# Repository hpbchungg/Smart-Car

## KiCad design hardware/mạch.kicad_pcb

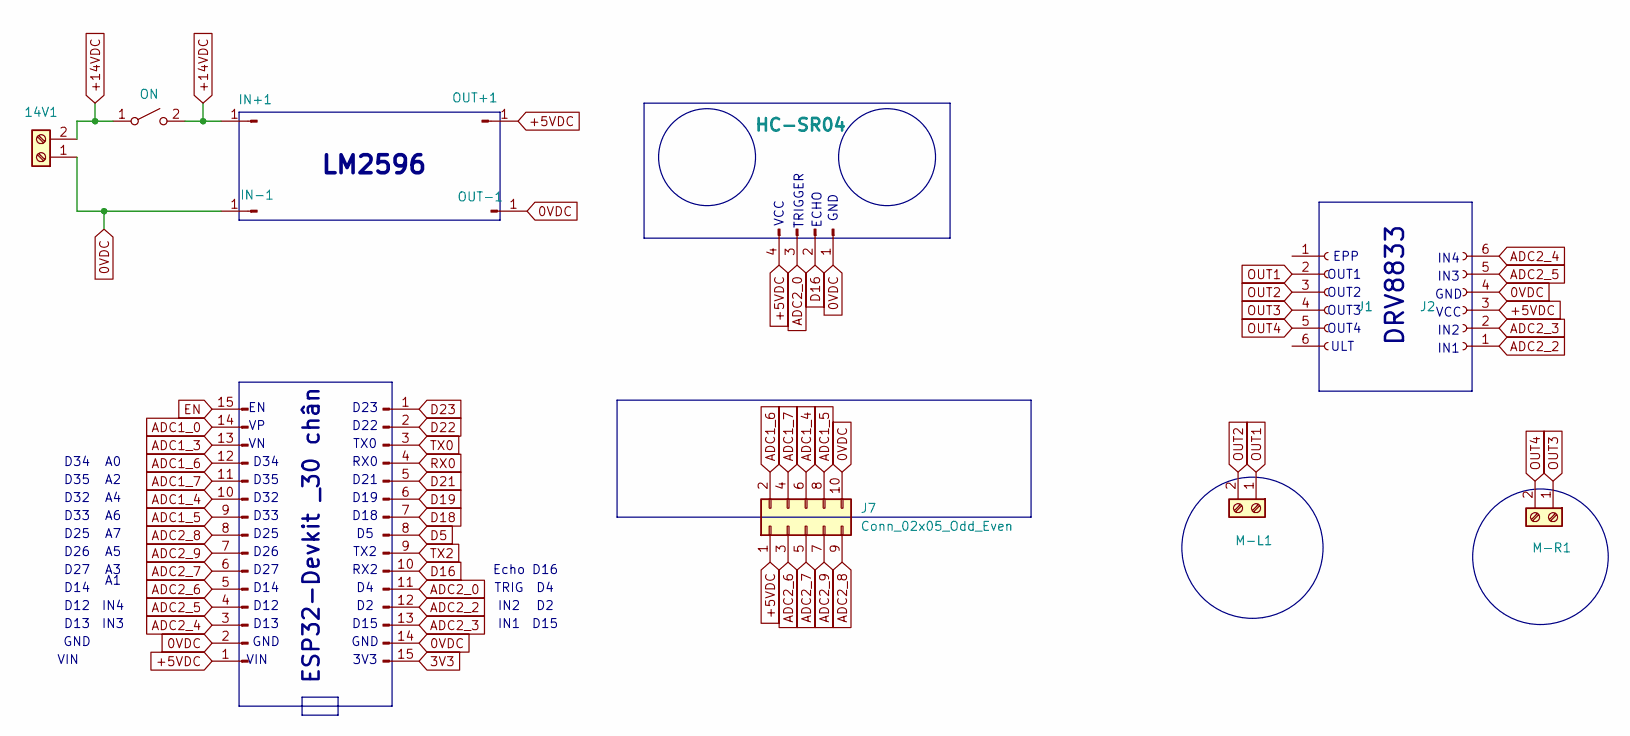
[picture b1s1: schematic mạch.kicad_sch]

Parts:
14V1: Screw_Terminal_01x02; TerminalBlock_Altech_AK300-2_P5.00mm
IN+1: Conn_01x01_Pin; PinHeader_1x01_P2.54mm_Vertical
IN-1: Conn_01x01_Pin; PinHeader_1x01_P2.54mm_Vertical
J1, J2: Conn_01x06_Socket; PinHeader_1x06_P2.54mm_Vertical
J3, J4: Conn_01x15_Pin; PinHeader_1x15_P2.54mm_Vertical
J5: HC-SR04; PinHeader_1x04_P2.54mm_Vertical
J7: Conn_02x05_Odd_Even; IDC-Header_2x05_P2.54mm_Vertical
M-L1: Screw_Terminal_01x02; TerminalBlock_Altech_AK300-2_P5.00mm
M-R1: Screw_Terminal_01x02; TerminalBlock_Altech_AK300-2_P5.00mm
OUT+1: Conn_01x01_Pin; PinHeader_1x01_P2.54mm_Vertical
OUT-1: Conn_01x01_Pin; PinHeader_1x01_P2.54mm_Vertical
SW1: ON; TerminalBlock_MetzConnect_Type171_RT13702HBWC_1x02_P7.50mm_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

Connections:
0VDC: 14V1.1, IN-1.1, J2.4, J3.2, J4.14, J5.1, J7.10, OUT-1.1
3V3: J4.15
+5VDC: J2.3, J3.1, J5.4, J7.1, OUT+1.1
+14VDC: 14V1.2, IN+1.1, SW1.1 (A), SW1.2 (B)
ADC1_0: J3.14
ADC1_3: J3.13
ADC1_4: J3.10, J7.6
ADC1_5: J3.9, J7.8
ADC1_6: J3.12, J7.2
ADC1_7: J3.11, J7.4
ADC2_0: J4.11, J5.3
ADC2_2: J2.1, J4.12
ADC2_3: J2.2, J4.13
ADC2_4: J2.6, J3.3
ADC2_5: J2.5, J3.4
ADC2_6: J3.5, J7.3
ADC2_7: J3.6, J7.5
ADC2_8: J3.8, J7.9
ADC2_9: J3.7, J7.7
D5: J4.8
D16: J4.10, J5.2
D18: J4.7
D19: J4.6
D21: J4.5
D22: J4.2
D23: J4.1
EN: J3.15
OUT1: J1.2, M-L1.1
OUT2: J1.3, M-L1.2
OUT3: J1.4, M-R1.1
OUT4: J1.5, M-R1.2
RX0: J4.4
TX0: J4.3
TX2: J4.9

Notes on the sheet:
D32
D34
IN2
D21
OUT4
GND
RX2
D25
VCC
D33
D12
D35
D19
3V3
D23
D13
TRIGGER
ECHO
DRV8833
IN2
TX0
D27
D14
OUT2
Echo
TRIG
D18
TX2
D22
OUT3
IN4
D26
IN1
VIN
D16
ESP32-Devkit _30 chân
D15
EPP
LM2596
RX0

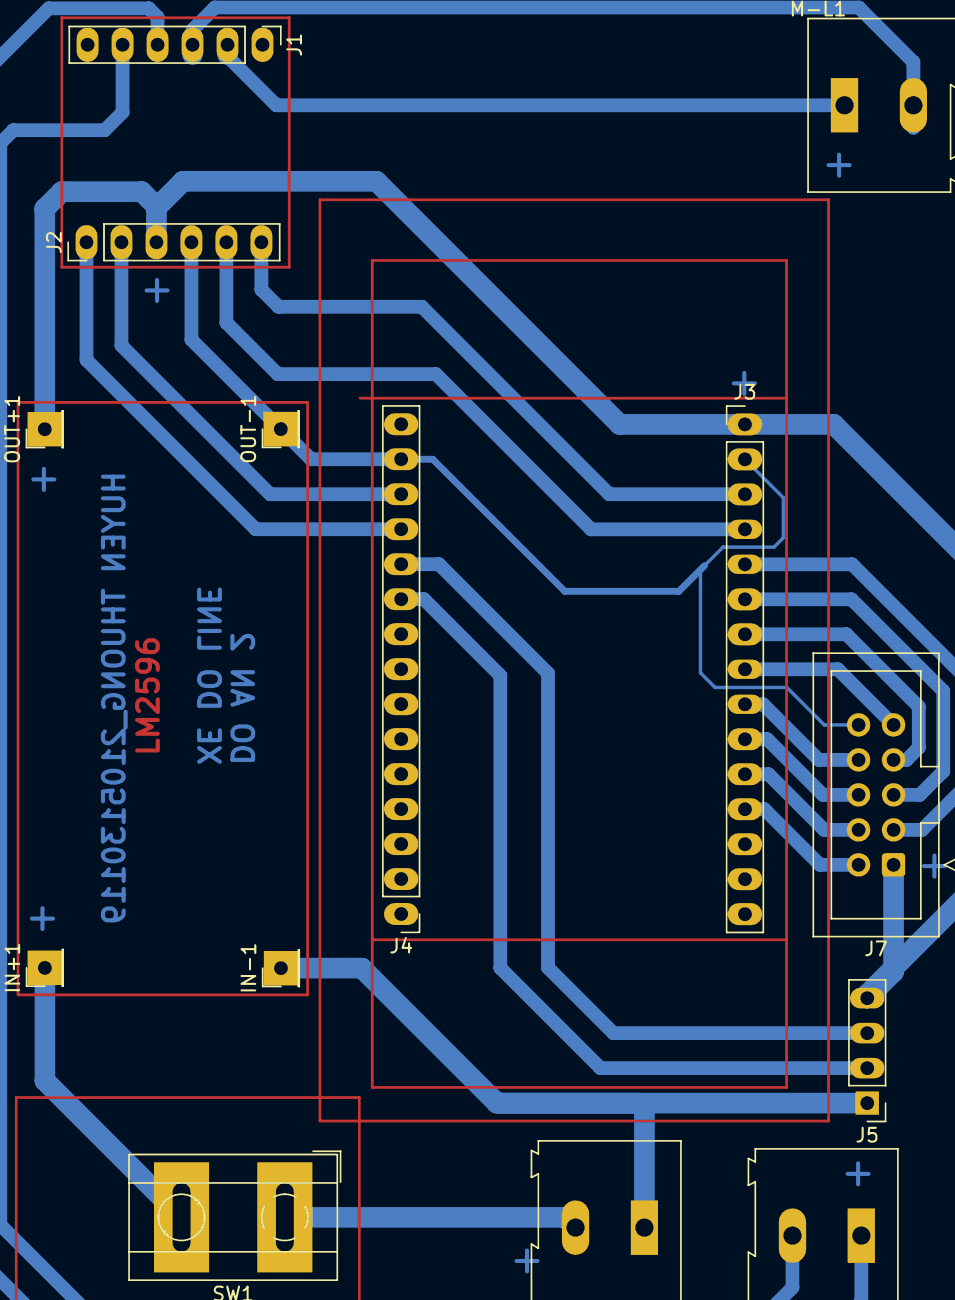
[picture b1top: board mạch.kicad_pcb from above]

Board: 2 copper layers, 14 parts (0 on the bottom side), 21 nets.

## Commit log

2025-12-06 add features checklist
2025-12-09 beta firmware
2025-12-09 add credential template file
2025-12-09 add ignore file
2025-12-11 test blynk
